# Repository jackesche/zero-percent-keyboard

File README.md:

# zero-percent-keyboard
 a keyboard

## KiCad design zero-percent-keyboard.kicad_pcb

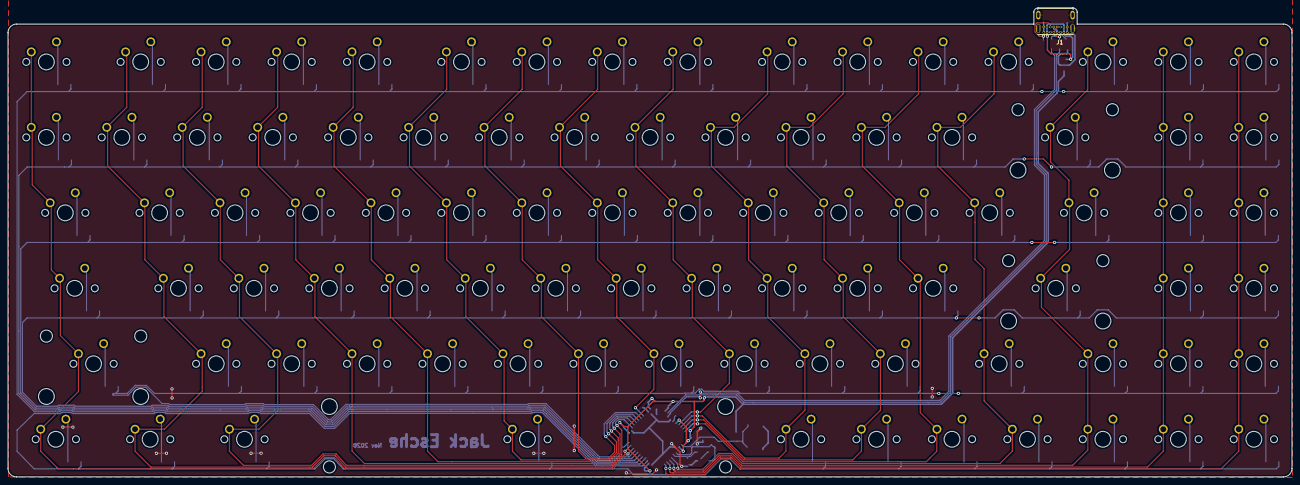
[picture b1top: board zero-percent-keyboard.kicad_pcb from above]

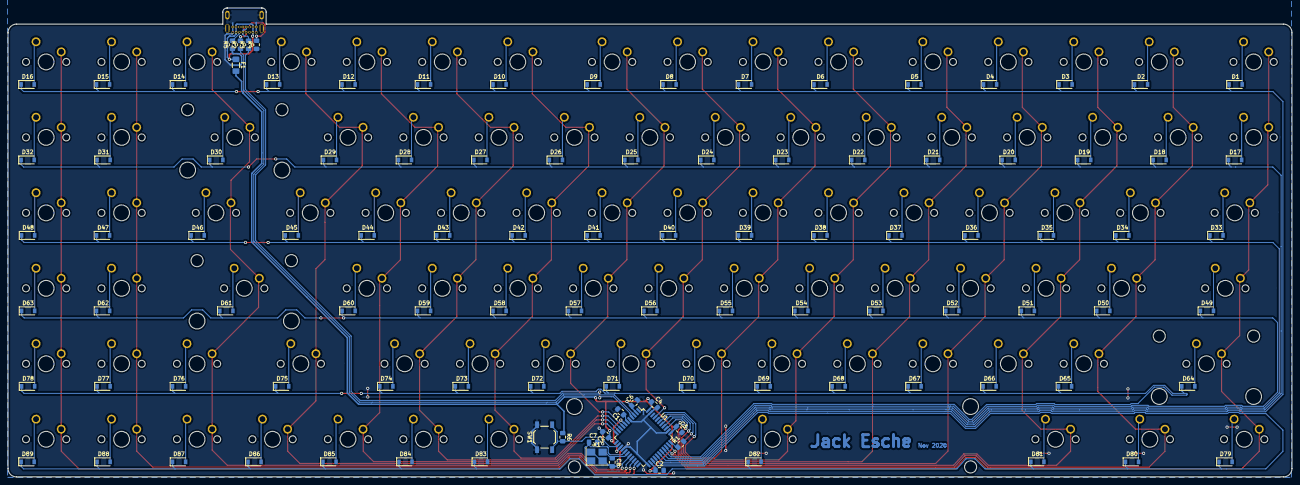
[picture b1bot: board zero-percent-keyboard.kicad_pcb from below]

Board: 2 copper layers, 324.1 x 118.4 mm, 197 parts (107 on the bottom side), 125 nets.

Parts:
C1: 1u; C_0805_2012Metric_Pad1.15x1.40mm_HandSolder
C2, C3, C4, C5: 0.1u; C_0805_2012Metric_Pad1.15x1.40mm_HandSolder
C6: 4.7u; C_0805_2012Metric_Pad1.15x1.40mm_HandSolder
C7, C8: 22p; C_0805_2012Metric_Pad1.15x1.40mm_HandSolder
D1, D2, D3, D4, D5, D6, D7, D8, D9, D10, D11, D12, D13, D14, D15, D16, D17, D18, D19, D20, D21, D22, D23, D24, D25, D26, D27, D28, D29, D30, D31, D32, D33, D34, D35, D36, D37, D38, D39, D40, D41, D42, D43, D44, D45, D46, D47, D48, D49, D50, D51, D52, D53, D54, D55, D56, D57, D58, D59, D60, D61, D62, D63, D64, D65, D66, D67, D68, D69, D70, D71, D72, D73, D74, D75, D76, D77, D78, D79, D80, D81, D82, D83, D84, D85, D86, D87, D88, D89: 22p; D_SOD-123
F1: 500mA; Fuse_1206_3216Metric_Pad1.42x1.75mm_HandSolder
J1: USB4085-GF-A_REVA; GCT_USB4085-GF-A_REVA
MX1, MX2, MX3, MX4, MX5, MX6, MX7, MX8, MX9, MX10, MX11, MX12, MX13, MX14, MX15, MX16, MX17, MX18, MX19, MX20, MX21, MX22, MX23, MX24, MX25, MX26, MX27, MX28, MX29, MX31, MX32, MX34, MX35, MX36, MX37, MX38, MX39, MX40, MX41, MX42, MX43, MX44, MX45, MX47, MX48, MX50, MX51, MX52, MX53, MX54, MX55, MX56, MX57, MX58, MX59, MX60, MX62, MX63, MX65, MX66, MX67, MX68, MX69, MX70, MX71, MX72, MX73, MX74, MX76, MX77, MX78, MX83, MX84, MX85, MX86, MX87, MX88, MX89: MX-NoLED; MXOnly-1U-NoLED
MX30: MX-NoLED; MXOnly-2U-NoLED
MX33, MX46: MX-NoLED; MXOnly-1.5U-NoLED
MX49, MX75: MX-NoLED; MXOnly-1.75U-NoLED
MX61, MX64: MX-NoLED; MXOnly-2.25U-NoLED
MX79, MX80, MX81: MX-NoLED; MXOnly-1.25U-NoLED
MX82: MX-NoLED; MXOnly-6.25U-ReversedStabilizers-NoLED
R1, R6: 10k; R_0805_2012Metric_Pad1.15x1.40mm_HandSolder
R2, R3: 22 ohm; R_0805_2012Metric_Pad1.15x1.40mm_HandSolder
R4, R5: 5.1k; R_0805_2012Metric_Pad1.15x1.40mm_HandSolder
SW1: SW_PUSH; SW_SPST_TL3342
U1: ATMEGA32U4; TQFP-44_10x10mm_P0.8mm
X1: XTAL_GND; Crystal_SMD_SeikoEpson_FA238-4Pin_3.2x2.5mm_HandSoldering

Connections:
+5V: C2.1, C3.1, C4.1, C5.1, C6.1, F1.2, R6.1, U1.2, U1.7, U1.14, U1.24, U1.34, U1.44
COL0: MX1.1, MX17.1, MX33.1, MX49.1, MX64.1, MX79.1, U1.31
COL1: MX2.1, MX18.1, MX34.1, MX50.1, MX65.1, MX80.1, U1.32
COL2: MX3.1, MX19.1, MX35.1, MX51.1, MX66.1, MX81.1, U1.36
COL3: MX4.1, MX20.1, MX36.1, MX52.1, MX67.1, U1.37
COL4: MX5.1, MX21.1, MX37.1, MX53.1, MX68.1, U1.38
COL5: MX6.1, MX22.1, MX38.1, MX54.1, MX69.1, MX82.1, U1.39
COL6: MX7.1, MX23.1, MX39.1, MX55.1, MX70.1, U1.40
COL7: MX8.1, MX24.1, MX40.1, MX56.1, MX71.1, U1.41
COL8: MX9.1, MX25.1, MX41.1, MX57.1, MX72.1, U1.8
COL9: MX10.1, MX26.1, MX42.1, MX58.1, MX73.1, MX83.1, U1.9
COL10: MX11.1, MX27.1, MX43.1, MX59.1, MX74.1, MX84.1, U1.10
COL11: MX12.1, MX28.1, MX44.1, MX60.1, MX85.1, U1.11
COL12: MX13.1, MX29.1, MX45.1, MX75.1, MX86.1, U1.18
COL13: MX14.1, MX30.1, MX46.1, MX61.1, MX76.1, MX87.1, U1.19
COL14: MX15.1, MX31.1, MX47.1, MX62.1, MX77.1, MX88.1, U1.20
COL15: MX16.1, MX32.1, MX48.1, MX63.1, MX78.1, MX89.1, U1.21
D+: R3.1, U1.4
D-: R2.1, U1.3
GND: C1.2, C2.2, C3.2, C4.2, C5.2, C6.2, C7.2, C8.2, J1.A1, J1.A12, J1.B1, J1.B12, J1.P1, J1.P2, J1.P3, J1.P4, R1.2, R4.1, R5.1, SW1.1, U1.5, U1.15, U1.23, U1.35, U1.43, X1.2, X1.4
unnamed: C1.1, U1.6
unnamed: D1.2, MX1.2
unnamed: D2.2, MX2.2
unnamed: D3.2, MX3.2
unnamed: D4.2, MX4.2
unnamed: D5.2, MX5.2
unnamed: D6.2, MX6.2
unnamed: D7.2, MX7.2
unnamed: D8.2, MX8.2
unnamed: D9.2, MX9.2
unnamed: D10.2, MX10.2
unnamed: D11.2, MX11.2
unnamed: D12.2, MX12.2
unnamed: D13.2, MX13.2
unnamed: D14.2, MX14.2
unnamed: D15.2, MX15.2
unnamed: D16.2, MX16.2
unnamed: D17.2, MX17.2
unnamed: D18.2, MX18.2
unnamed: D19.2, MX19.2
unnamed: D20.2, MX20.2
unnamed: D21.2, MX21.2
unnamed: D22.2, MX22.2
unnamed: D23.2, MX23.2
unnamed: D24.2, MX24.2
unnamed: D25.2, MX25.2
unnamed: D26.2, MX26.2
unnamed: D27.2, MX27.2
unnamed: D28.2, MX28.2
unnamed: D29.2, MX29.2
unnamed: D30.2, MX30.2
unnamed: D31.2, MX31.2
unnamed: D32.2, MX32.2
unnamed: D33.2, MX33.2
unnamed: D34.2, MX34.2
unnamed: D35.2, MX35.2
unnamed: D36.2, MX36.2
unnamed: D37.2, MX37.2
unnamed: D38.2, MX38.2
unnamed: D39.2, MX39.2
unnamed: D40.2, MX40.2
unnamed: D41.2, MX41.2
unnamed: D42.2, MX42.2
unnamed: D43.2, MX43.2
unnamed: D44.2, MX44.2
unnamed: D45.2, MX45.2
unnamed: D46.2, MX46.2
unnamed: D47.2, MX47.2
unnamed: D48.2, MX48.2
unnamed: D49.2, MX49.2
unnamed: D50.2, MX50.2
unnamed: D51.2, MX51.2
unnamed: D52.2, MX52.2
unnamed: D53.2, MX53.2
unnamed: D54.2, MX54.2
unnamed: D55.2, MX55.2
unnamed: D56.2, MX56.2
unnamed: D57.2, MX57.2
unnamed: D58.2, MX58.2
unnamed: D59.2, MX59.2
unnamed: D60.2, MX60.2
unnamed: D61.2, MX61.2
unnamed: D62.2, MX62.2
unnamed: D63.2, MX63.2
unnamed: D64.2, MX64.2
unnamed: D65.2, MX65.2
unnamed: D66.2, MX66.2
unnamed: D67.2, MX67.2
unnamed: D68.2, MX68.2
unnamed: D69.2, MX69.2
unnamed: D70.2, MX70.2
unnamed: D71.2, MX71.2
unnamed: D72.2, MX72.2
unnamed: D73.2, MX73.2
unnamed: D74.2, MX74.2
unnamed: D75.2, MX75.2
unnamed: D76.2, MX76.2
unnamed: D77.2, MX77.2
unnamed: D78.2, MX78.2
unnamed: D79.2, MX79.2
unnamed: D80.2, MX80.2
unnamed: D81.2, MX81.2
unnamed: D82.2, MX82.2
unnamed: D83.2, MX83.2
unnamed: D84.2, MX84.2
unnamed: D85.2, MX85.2
unnamed: D86.2, MX86.2
unnamed: D87.2, MX87.2
unnamed: D88.2, MX88.2
unnamed: D89.2, MX89.2
unnamed: J1.A5, R5.2
unnamed: J1.A6, J1.B6, R3.2
unnamed: J1.A7, J1.B7, R2.2
unnamed: J1.B5, R4.2
unnamed: R1.1, U1.33
RESET: R6.2, SW1.2, U1.13
ROW0: D1.1, D2.1, D3.1, D4.1, D5.1, D6.1, D7.1, D8.1, D9.1, D10.1, D11.1, D12.1, D13.1, D14.1, D15.1, D16.1, U1.26
ROW1: D17.1, D18.1, D19.1, D20.1, D21.1, D22.1, D23.1, D24.1, D25.1, D26.1, D27.1, D28.1, D29.1, D30.1, D31.1, D32.1, U1.27
ROW2: D33.1, D34.1, D35.1, D36.1, D37.1, D38.1, D39.1, D40.1, D41.1, D42.1, D43.1, D44.1, D45.1, D46.1, D47.1, D48.1, U1.28
ROW3: D49.1, D50.1, D51.1, D52.1, D53.1, D54.1, D55.1, D56.1, D57.1, D58.1, D59.1, D60.1, D61.1, D62.1, D63.1, U1.29
ROW4: D64.1, D65.1, D66.1, D67.1, D68.1, D69.1, D70.1, D71.1, D72.1, D73.1, D74.1, D75.1, D76.1, D77.1, D78.1, U1.30
ROW5: D79.1, D80.1, D81.1, D82.1, D83.1, D84.1, D85.1, D86.1, D87.1, D88.1, D89.1, U1.25
VCC: F1.1, J1.A4, J1.A9, J1.B4, J1.B9
XTAL1: C7.1, U1.16, X1.1
XTAL2: C8.1, U1.17, X1.3

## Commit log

2020-11-22 Matrix layout
2020-11-22 Rename file
2020-11-24 Layout change
2020-11-24 Progress
2020-11-25 Route traces
2020-11-26 Rearrange rows and columns in schematic
2020-11-27 Finished PCB
2021-01-11 Summary
2021-01-11 Add Title
